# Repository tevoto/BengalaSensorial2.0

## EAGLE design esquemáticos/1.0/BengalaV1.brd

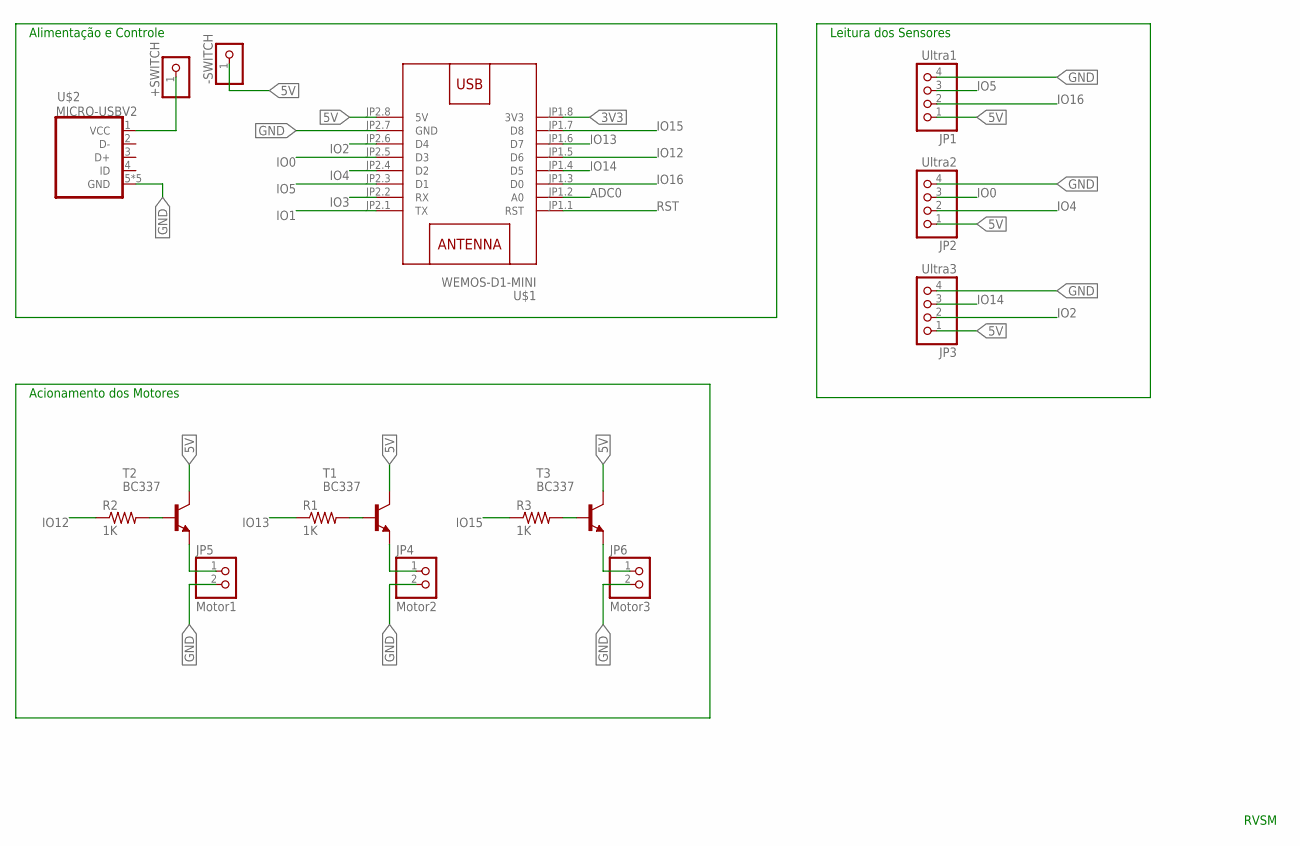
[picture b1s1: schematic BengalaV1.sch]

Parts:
+SWITCH: PINHD-1X1; 1X01
-SWITCH: PINHD-1X1; 1X01
JP1: Ultra1; 1X04
JP2: Ultra2; 1X04
JP3: Ultra3; 1X04
JP4: Motor2; 1X02
JP5: Motor1; 1X02
JP6: Motor3; 1X02
R1, R2, R3: 1K; 0204/7
T1, T2, T3: BC337; TO92
U$1: WEMOS-D1-MINI
U$2: MICRO-USBV2; MICRO-USB-2

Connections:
3V3: U$1.JP1.8 (3V3)
5V: -SWITCH.1, JP1.1, JP2.1, JP3.1, T1.3 (C), T2.3 (C), T3.3 (C), U$1.JP2.8 (5V)
ADC0: U$1.JP1.2 (A0)
GND: JP1.4, JP2.4, JP3.4, JP4.2, JP5.2, JP6.2, U$1.JP2.7 (GND), U$2.5 (GND), U$2.P$1 (GND), U$2.P$2 (GND), U$2.P$3 (GND), U$2.P$4 (GND)
IO0: JP2.3, U$1.JP2.5 (D3)
IO1: U$1.JP2.1 (TX)
IO2: JP3.2, U$1.JP2.6 (D4)
IO3: U$1.JP2.2 (RX)
IO4: JP2.2, U$1.JP2.4 (D2)
IO5: JP1.3, U$1.JP2.3 (D1)
IO12: R2.1, U$1.JP1.5 (D6)
IO13: R1.1, U$1.JP1.6 (D7)
IO14: JP3.3, U$1.JP1.4 (D5)
IO15: R3.1, U$1.JP1.7 (D8)
IO16: JP1.2, U$1.JP1.3 (D0)
unnamed: R1.2, T1.2 (B)
unnamed: +SWITCH.1, U$2.1 (VCC)
unnamed: JP4.1, T1.1 (E)
unnamed: R2.2, T2.2 (B)
unnamed: JP5.1, T2.1 (E)
unnamed: R3.2, T3.2 (B)
unnamed: JP6.1, T3.1 (E)
RST: U$1.JP1.1 (RST)

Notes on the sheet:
RVSM
Alimentação e Controle
Leitura dos Sensores
Acionamento dos Motores

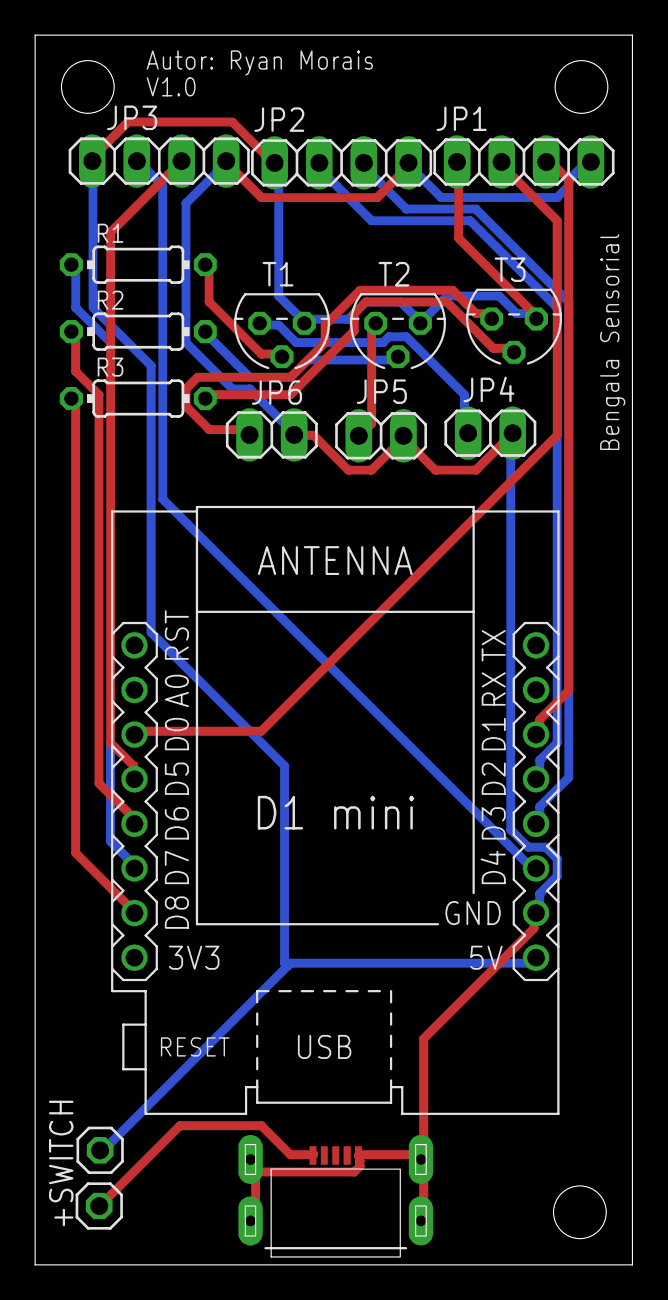
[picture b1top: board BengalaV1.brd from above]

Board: 2 copper layers, 34.0 x 70.0 mm, 16 parts (0 on the bottom side), 18 nets.

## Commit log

2022-07-15 (NOVO)Esquemático Bengala
    novo esquemático como padrão de cores diferente

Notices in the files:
parts and their libraries:
diy-modules: Released under the Creative Commons Attribution 4.0 International License: http://creativecommons.org/licenses/by/4.0
